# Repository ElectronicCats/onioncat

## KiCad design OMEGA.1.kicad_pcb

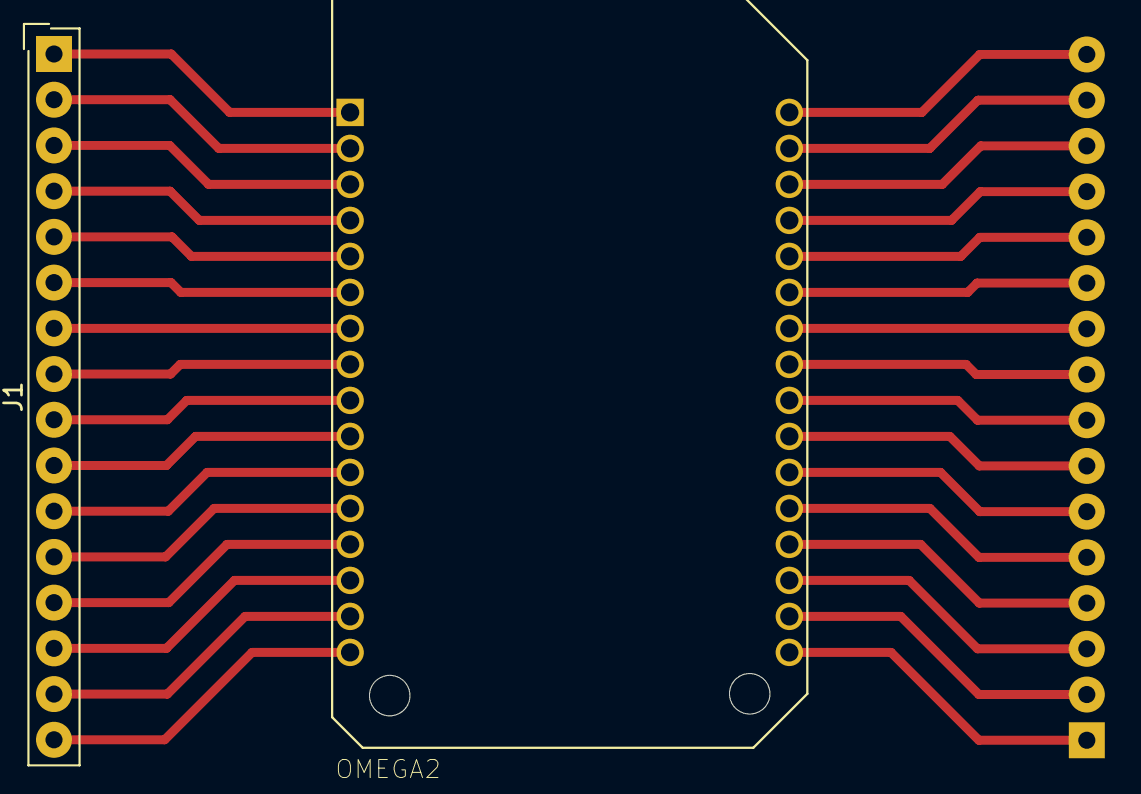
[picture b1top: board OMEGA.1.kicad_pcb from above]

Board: 2 copper layers, 3 parts (1 on the bottom side), 32 nets.

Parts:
J1, J2: Conn_01x16; SL-116-X-XX_1x16
U1: OMEGA2; XCVR_OMEGA2

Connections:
unnamed: J1.1, U1.1
unnamed: J1.2, U1.2
unnamed: J1.3, U1.3
unnamed: J1.4, U1.4
unnamed: J1.5, U1.5
unnamed: J1.6, U1.6
unnamed: J1.7, U1.7
unnamed: J1.8, U1.8
unnamed: J1.9, U1.9
unnamed: J1.10, U1.10
unnamed: J1.11, U1.11
unnamed: J1.12, U1.12
unnamed: J1.13, U1.13
unnamed: J1.14, U1.14
unnamed: J1.15, U1.15
unnamed: J1.16, U1.16
unnamed: J2.1, U1.17
unnamed: J2.2, U1.18
unnamed: J2.3, U1.19
unnamed: J2.4, U1.20
unnamed: J2.5, U1.21
unnamed: J2.6, U1.22
unnamed: J2.7, U1.23
unnamed: J2.8, U1.24
unnamed: J2.9, U1.25
unnamed: J2.10, U1.26
unnamed: J2.11, U1.27
unnamed: J2.12, U1.28
unnamed: J2.13, U1.29
unnamed: J2.14, U1.30
unnamed: J2.15, U1.31
unnamed: J2.16, U1.32

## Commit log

2017-10-30 OMEGA CHIO
    Adaptador solo pines
